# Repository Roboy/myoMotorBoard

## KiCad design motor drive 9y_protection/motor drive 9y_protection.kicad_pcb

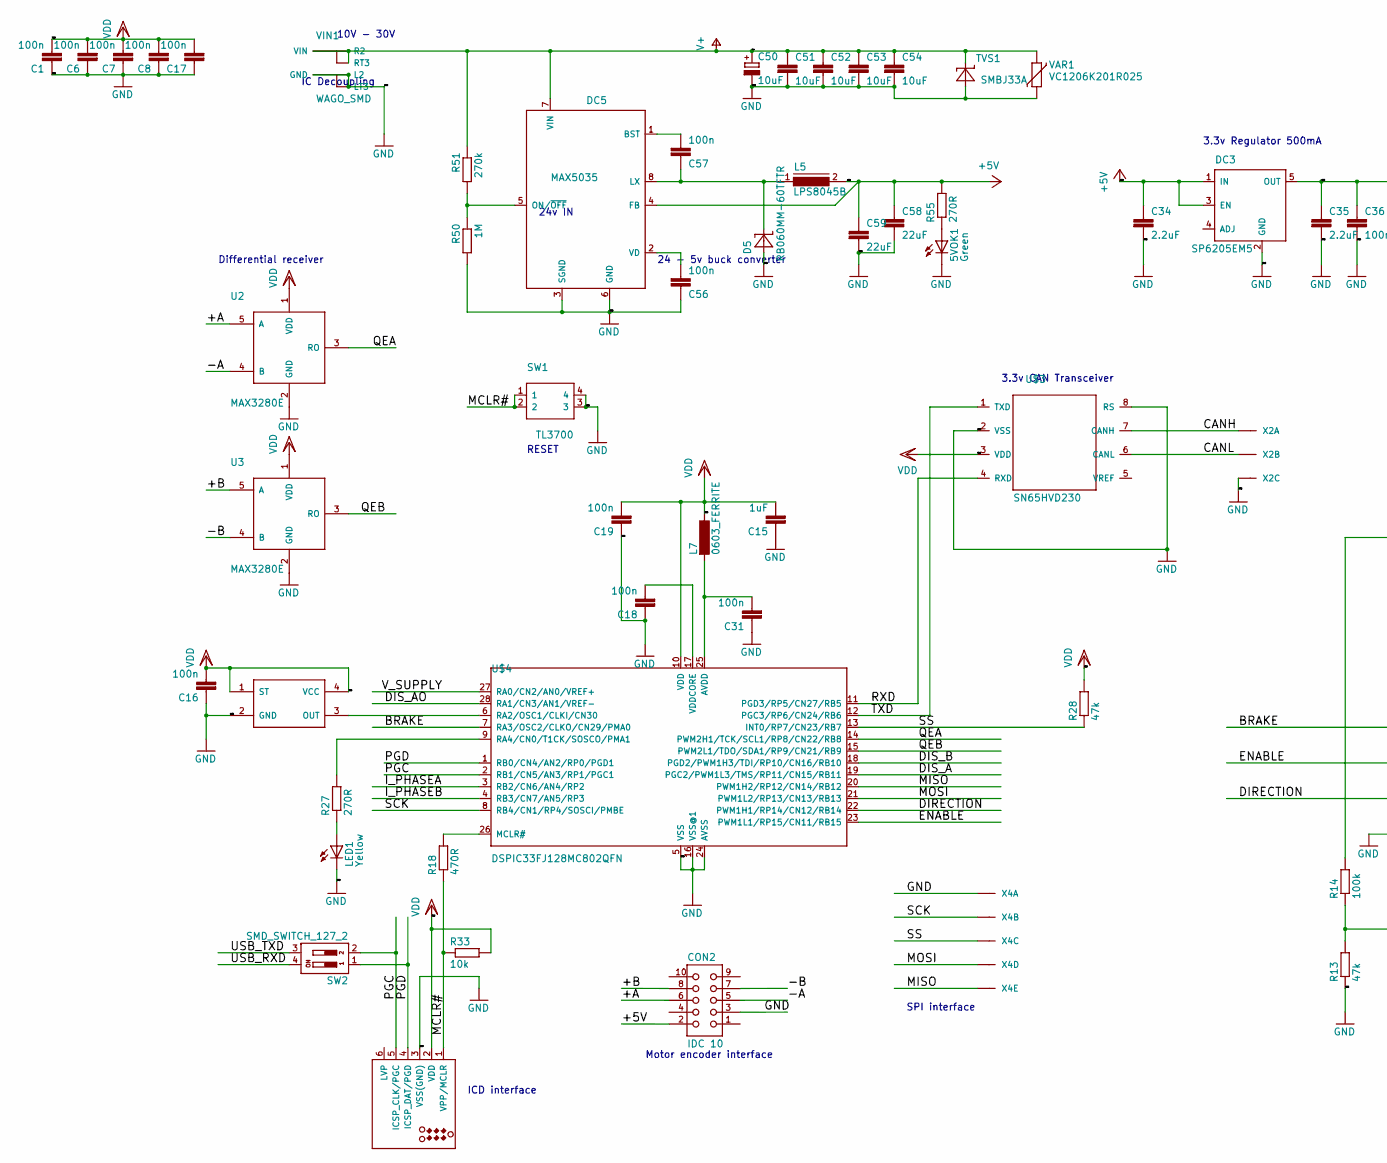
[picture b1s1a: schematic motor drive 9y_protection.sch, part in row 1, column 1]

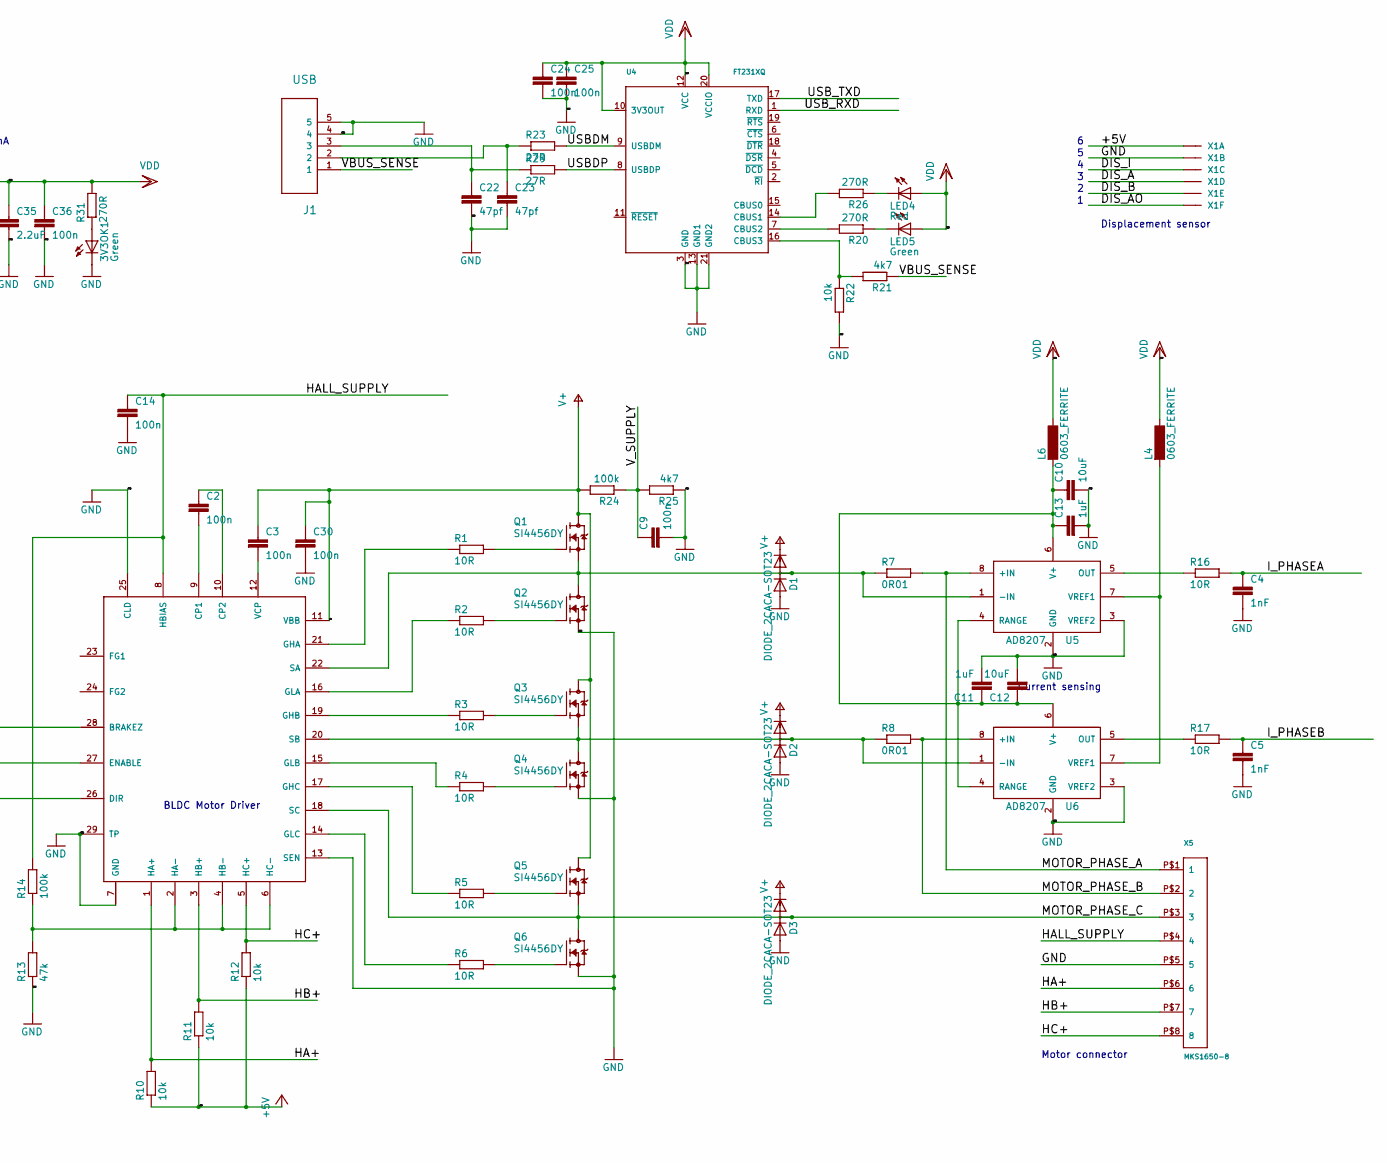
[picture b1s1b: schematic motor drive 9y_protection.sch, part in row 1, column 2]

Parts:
3V3OK1, 5VOK1: Green; CHIPLED_0603
C1, C2, C3, C6, C7, C8, C9, C14, C16, C17, C18, C19, C24, C25, C30, C31, C36, C56, C57: 100n; C0402K
C4, C5: 1nF; C0402K
C10, C12: 10uF; C0805K
C11, C13, C15: 1uF; C0603K
C22, C23: 47pf; C0402K
C34, C35: 2.2uF; C1210
C50: 10uF; PANASONIC_D
C51, C52, C53, C54: 10uF; C1210
C58, C59: 22uF; C1210
CON2: IDC 10; MIRCO_MATCH
D1, D2, D3: DIODE_2CACA-SOT23; SOT23
D5: RB060MM-60TFTR; SOD123
DC3: SP6205EM5; SOT23-5
DC5: MAX5035; SOIC8
J1: USB; MOLEX_47346-0001
J3: TAG Connect; TC2030-MCP-NL
L4, L6, L7: 0603_FERRITE; R0603
L5: LPS8045B; LPS8045B-104MRB_SPULE
LED1: Yellow; CHIPLED_0603
LED4: Red; CHIPLED_0603
LED5: Green; CHIPLED_0603
Q1, Q2, Q3, Q4, Q5, Q6: SI4456DY; SO8
R1, R2, R3, R4, R5, R6, R16, R17: 10R; R0603
R7, R8: 0R01; R2512
R10, R11, R12, R22, R33: 10k; R0402
R13, R28: 47k; R0402
R14, R24: 100k; R0402
R18: 470R; R0402
R20, R26, R27, R31, R55: 270R; R0402
R21, R25: 4k7; R0402
R23, R29: 27R; R0402
R50: 1M; R0402
R51: 270k; R0402
SW1: TL3700
SW2: SMD_SWITCH_127_2
TVS1: SMBJ33A; DIODE
U1: A4931; QFN-28-NEW
U2, U3: MAX3280E; SOT23-5L
U4: FT231XQ; QFN20
U5, U6: AD8207; SO8
U$3: SN65HVD230; 999
U$4: DSPIC33FJ128MC802QFN; QFN-S28-6X6
U$6: SG-310
VAR1: VC1206K201R025; CT_CN1206
VIN1: WAGO_SMD
X1: ?M06B-SRSS-TBB; BM06B-SRSS-TB
X2: ?M03B-SRSS-TBB; BM03B-SRSS-TB
X4: ?M05B-SRSS-TBB; BM05B-SRSS-TB
X5: MKS1650-8; MKS1650

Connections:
+5V: C34.1, C58.1, C59.1, DC3.1 (IN), DC3.3 (EN), DC5.4 (FB), L5.2, R10.1, R11.1, R12.1, R55.2, X1.1
/+A: U2.5 (A)
/+B: U3.5 (A)
/-A: CON2.5, U2.4 (B)
/-B: U3.4 (B)
/BRAKE: U1.28 (BRAKEZ), U$4.7 (RA3/OSC2/CLKO/CN29/PMA0)
/CANH: U$3.7 (CANH), X2.1
/CANL: U$3.6 (CANL), X2.2
/DIRECTION: U1.26 (DIR), U$4.22 (PWM1H1/RP14/CN12/RB14)
/DIS_A: U$4.19 (PGC2/PWM1L3/TMS/RP11/CN15/RB11), X1.4
/DIS_AO: U$4.28 (RA1/CN3/AN1/VREF-), X1.6
/DIS_B: U$4.18 (PGD2/PWM1H3/TDI/RP10/CN16/RB10), X1.5
/DIS_I: X1.3
/ENABLE: U1.27 (ENABLE), U$4.23 (PWM1L1/RP15/CN11/RB15)
/HA+: R10.2, U1.1 (HA+), X5.P$6 (6)
/HALL_SUPPLY: C14.1, R14.2, U1.8 (HBIAS), X5.P$4 (4)
/HB+: R11.2, U1.3 (HB+), X5.P$7 (7)
/HC+: R12.2, U1.5 (HC+), X5.P$8 (8)
/I_PHASEA: C4.1, R16.2, U$4.3 (RB2/CN6/AN4/RP2)
/I_PHASEB: C5.1, R17.2, U$4.4 (RB3/CN7/AN5/RP3)
/MCLR#: J3.1 (VPP/MCLR), R18.1, R33.1, SW1.1, SW1.2
/MISO: U$4.20 (PWM1H2/RP12/CN14/RB12), X4.5
/MOSI: U$4.21 (PWM1L2/RP13/CN13/RB13), X4.4
/MOTOR_PHASE_A: R7.2, U5.8 (+IN), X5.P$1 (1)
/MOTOR_PHASE_B: R8.2, U6.8 (+IN), X5.P$2 (2)
/MOTOR_PHASE_C: D3.3 (AC), Q5.1 (S), Q5.2 (S), Q5.3 (S), Q6.5 (D), Q6.6 (D), Q6.7 (D), Q6.8 (D), U1.18 (SC), X5.P$3 (3)
/PGC: J3.5 (ICSP_CLK/PGC), SW2.2, U$4.2 (RB1/CN5/AN3/RP1/PGC1)
/PGD: J3.4 (ICSP_DAT/PGD), SW2.1, U$4.1 (RB0/CN4/AN2/RP0/PGD1)
/QEA: U2.3 (RO), U$4.14 (PWM2H1/TCK/SCL1/RP8/CN22/RB8)
/QEB: U3.3 (RO), U$4.15 (PWM2L1/TDO/SDA1/RP9/CN21/RB9)
/RXD: U$3.4 (RXD), U$4.11 (PGD3/RP5/CN27/RB5)
/SCK: U$4.8 (RB4/CN1/RP4/SOSCI/PMBE), X4.2
/SS: R28.1, U$4.13 (INT0/RP7/CN23/RB7), X4.3
/TXD: U$3.1 (TXD), U$4.12 (PGC3/RP6/CN24/RB6)
/USBDM: R23.2, U4.9 (USBDM)
/USBDP: R29.2, U4.8 (USBDP)
/USB_RXD: SW2.4, U4.1 (RXD)
/USB_TXD: SW2.3, U4.17 (TXD)
/VBUS_SENSE: J1.1, R21.1
/V_SUPPLY: C9.1, R24.1, R25.2, U$4.27 (RA0/CN2/AN0/VREF+)
unnamed: 3V3OK1.A, R31.1
unnamed: 5VOK1.A, R55.1
unnamed: C2.1, U1.10 (CP2)
unnamed: C2.2, U1.9 (CP1)
unnamed: C3.2, U1.12 (VCP)
unnamed: C10.1, C11.1, C12.1, C13.1, L6.2, U5.4 (RANGE), U5.6 (V+), U6.4 (RANGE), U6.6 (V+)
unnamed: C18.2, U$4.17 (VDDCORE)
unnamed: C22.1, J1.3, R29.1
unnamed: C23.1, J1.2, R23.1
unnamed: C31.2, L7.2, U$4.25 (AVDD)
unnamed: C56.2, DC5.2 (VD)
unnamed: C57.1, D5.C, DC5.8 (LX), L5.1
unnamed: C57.2, DC5.1 (BST)
unnamed: D1.3 (AC), Q1.1 (S), Q1.2 (S), Q1.3 (S), Q2.5 (D), Q2.6 (D), Q2.7 (D), Q2.8 (D), R7.1, U1.22 (SA), U5.1 (-IN)
unnamed: D2.3 (AC), Q3.1 (S), Q3.2 (S), Q3.3 (S), Q4.5 (D), Q4.6 (D), Q4.7 (D), Q4.8 (D), R8.1, U1.20 (SB), U6.1 (-IN)
unnamed: DC5.5 (ON/~OFF), R50.1, R51.2
unnamed: L4.2, U5.7 (VREF1), U6.7 (VREF1)
unnamed: LED1.A, R27.1
unnamed: LED4.C, R26.1
unnamed: LED5.C, R20.1
unnamed: Q1.4 (G), R1.2
unnamed: Q2.4 (G), R2.2
unnamed: Q3.4 (G), R3.2
unnamed: Q4.4 (G), R4.2
unnamed: Q5.4 (G), R5.2
unnamed: Q6.4 (G), R6.2
unnamed: R1.1, U1.21 (GHA)
unnamed: R2.1, U1.16 (GLA)
unnamed: R3.1, U1.19 (GHB)
unnamed: R4.1, U1.15 (GLB)
unnamed: R5.1, U1.17 (GHC)
unnamed: R6.1, U1.14 (GLC)
unnamed: R13.2, R14.1, U1.2 (HA-), U1.4 (HB-), U1.6 (HC-)
unnamed: R16.1, U5.5 (OUT)
unnamed: R17.1, U6.5 (OUT)
unnamed: R18.2, U$4.26 (MCLR#)
unnamed: R20.2, U4.7 (CBUS2)
unnamed: R21.2, R22.1, U4.16 (CBUS3)
unnamed: R26.2, U4.14 (CBUS1)
unnamed: R27.2, U$4.9 (RA4/CN0/T1CK/SOSCO/PMA1)
unnamed: U$4.6 (RA2/OSC1/CLKI/CN30), U$6.3 (OUT)
V+: C3.1, C30.1, C50.+, C51.1, C52.1, C53.1, C54.1, D1.2 (C), D2.2 (C), D3.2 (C), DC5.7 (VIN), Q1.5 (D), Q1.6 (D), Q1.7 (D), Q1.8 (D), Q3.5 (D), Q3.6 (D), Q3.7 (D), Q3.8 (D), Q5.5 (D), Q5.6 (D), Q5.7 (D), Q5.8 (D), R24.2, R51.1, TVS1.1 (C), U1.11 (VBB), VAR1.1, VIN1.R1 (VIN), VIN1.R2, VIN1.R3 (RT3)
VDD: C1.2, C6.2, C7.2, C8.2, C15.2, C16.2, C17.2, C19.2, C24.1, C25.1, C35.1, C36.1, DC3.5 (OUT), J3.2 (VDD), L4.1, L6.1, L7.1, LED4.A, LED5.A, R28.2, R31.2, R33.2, U2.1 (VDD), U3.1 (VDD), U4.10 (3V3OUT), U4.12 (VCC), U4.20 (VCCIO), U$3.3 (VDD), U$4.10 (VDD), U$6.1 (ST), U$6.4 (VCC)

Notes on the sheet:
Displacement sensor
3.3v Regulator 500mA
24 - 5v buck converter
Differential receiver
ICD interface
Motor encoder interface
SPI interface
BLDC Motor Driver
Current sensing
Motor connector
3.3v CAN Transceiver
24v IN
RESET
IC Decoupling
10V - 30V

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
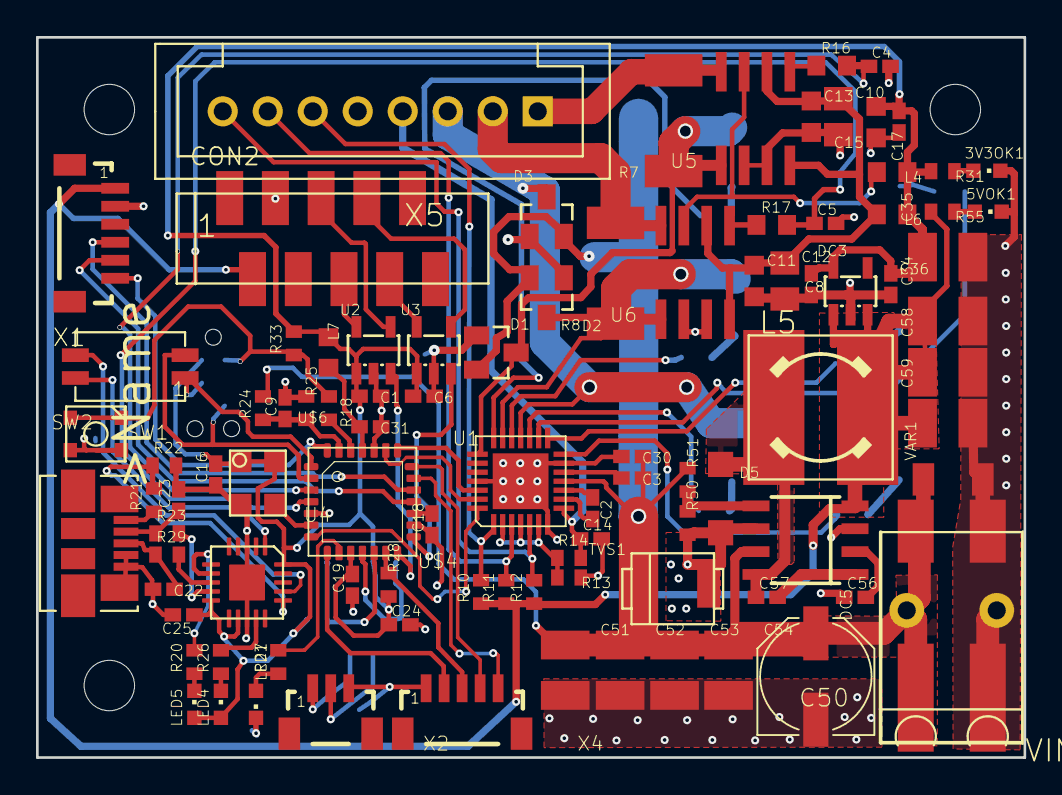
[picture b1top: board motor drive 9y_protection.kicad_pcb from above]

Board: 2 copper layers, 54.9 x 40.0 mm, 113 parts (0 on the bottom side), 80 nets.

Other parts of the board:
@HOLE0, @HOLE1, @HOLE2: (no value)

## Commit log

2019-08-27 converted to kicad

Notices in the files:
parts and their libraries:
tag-connect: ©2009 ROFA.cz - modified and updated by Robert Darlington ‹rdarlington@gmail.com›
